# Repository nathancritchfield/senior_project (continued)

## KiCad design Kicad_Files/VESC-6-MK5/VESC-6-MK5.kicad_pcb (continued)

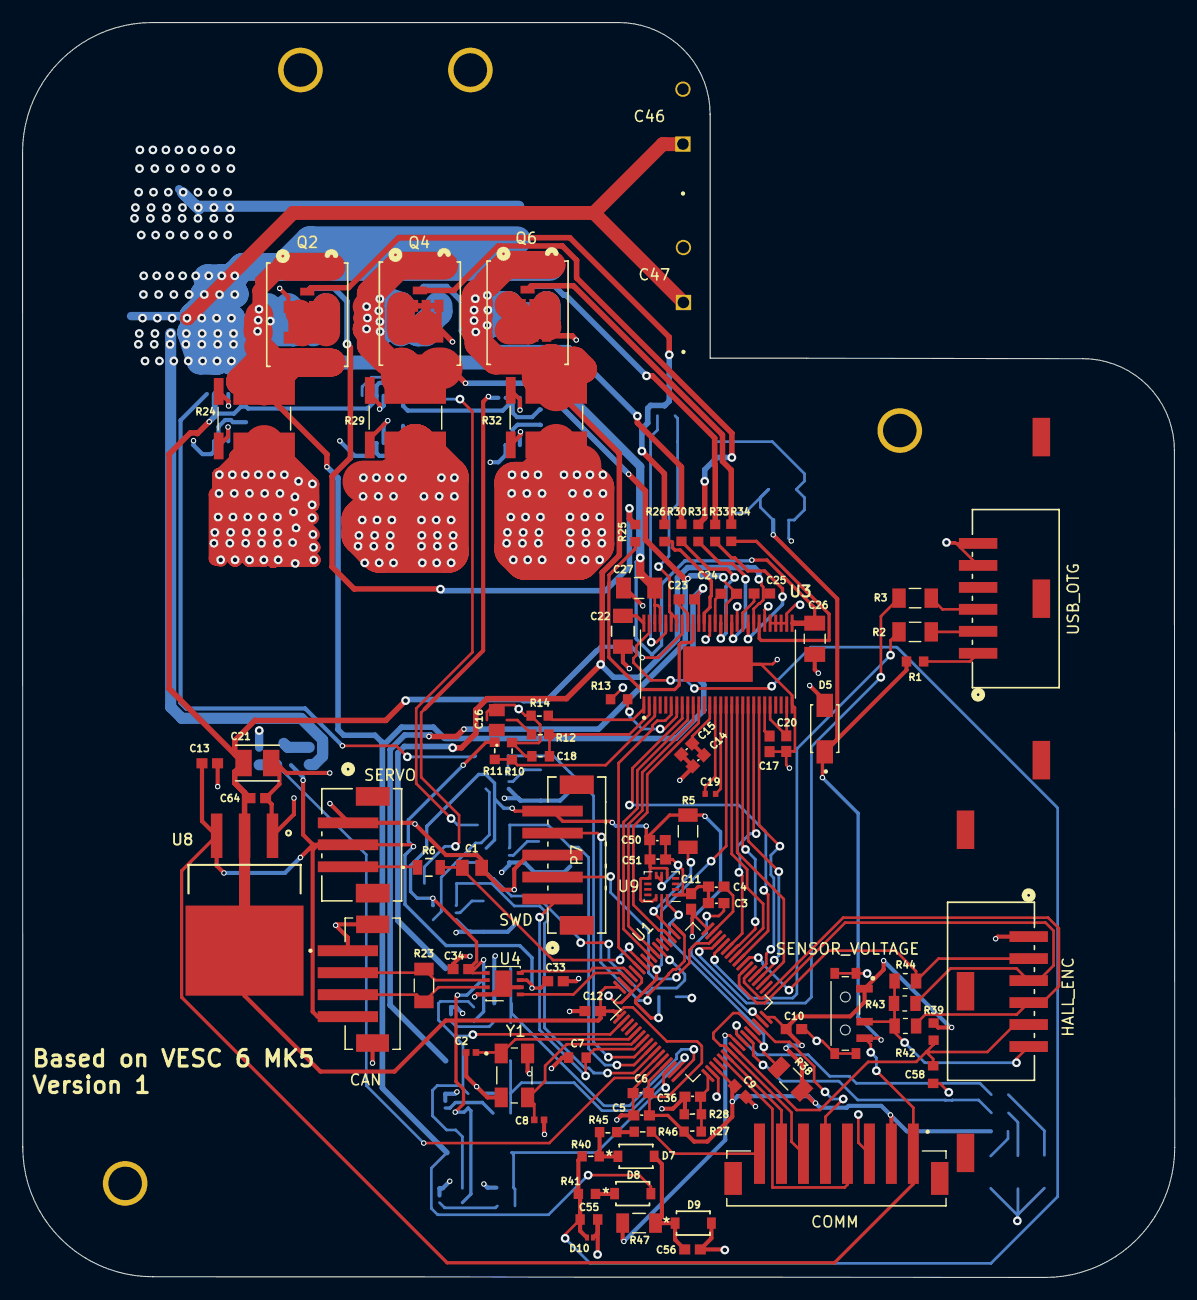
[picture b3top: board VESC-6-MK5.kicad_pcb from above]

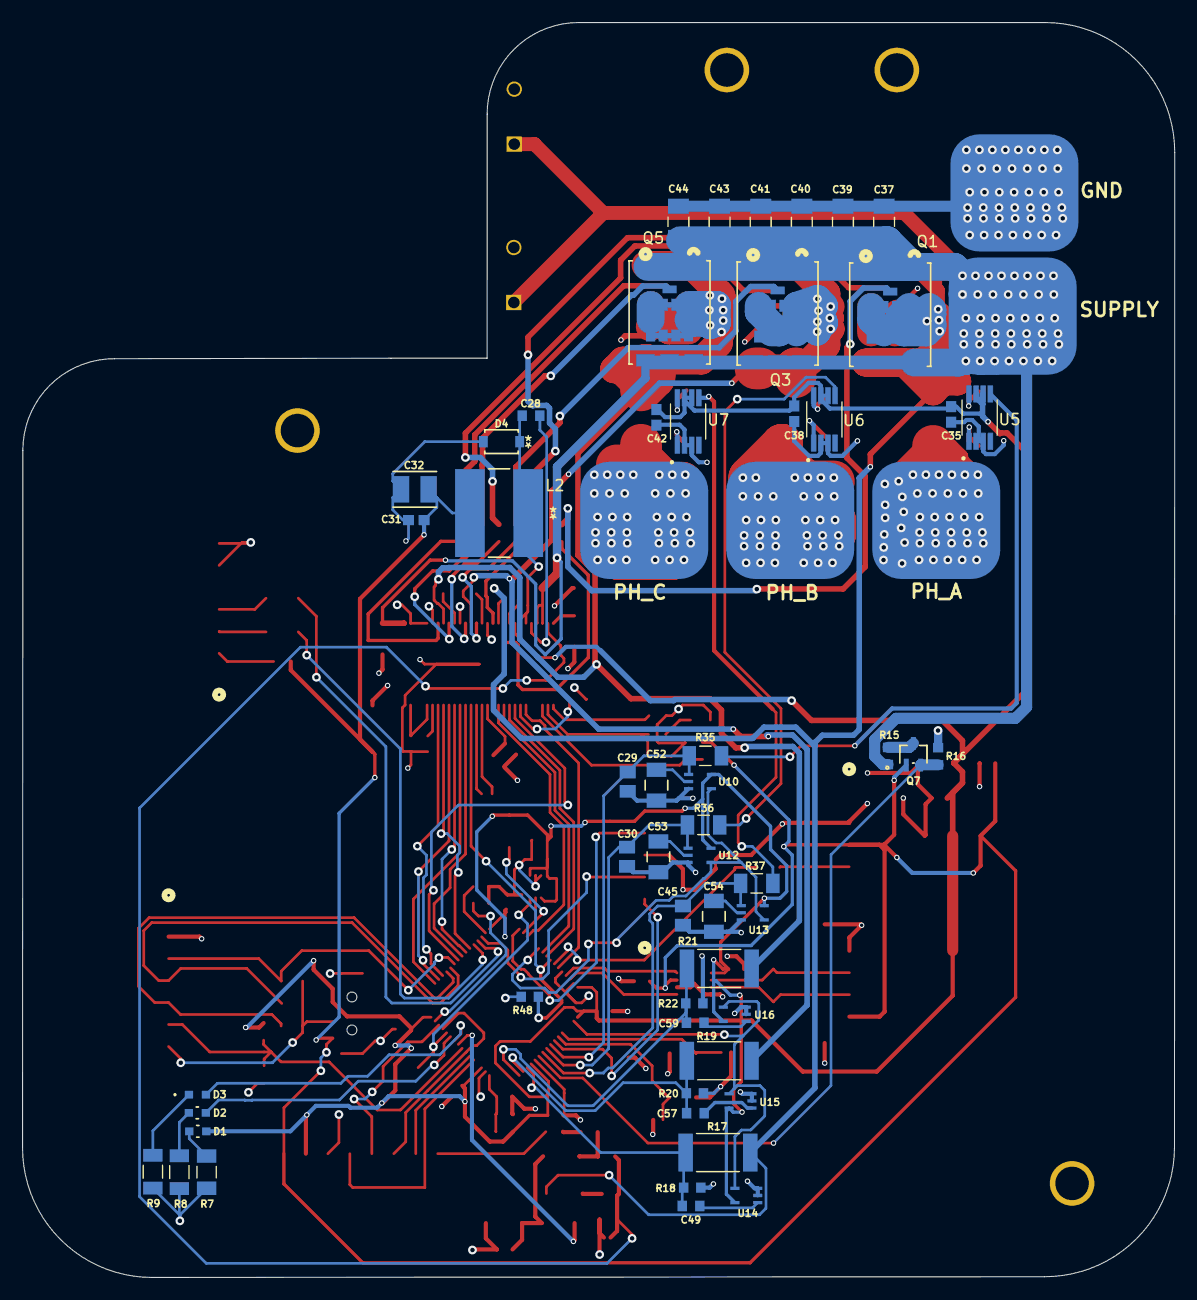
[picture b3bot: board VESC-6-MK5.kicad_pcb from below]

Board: 4 copper layers, 104.8 x 114.2 mm, 150 parts (59 on the bottom side), 117 nets.

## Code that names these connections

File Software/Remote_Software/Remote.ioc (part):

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Mcu.Name=STM32G030F6Px
Mcu.Package=TSSOP20
Mcu.UserName=STM32G030F6Px
PA0.GPIOParameters=GPIO_Speed
PA0.GPIO_Speed=GPIO_SPEED_FREQ_HIGH
PA0.Mode=Simplex_Bidirectional_Master
PA0.Signal=SPI2_SCK
PA1.GPIOParameters=GPIO_Label
PA1.GPIO_Label=Analog_In
PA1.Mode=IN1
PA1.Signal=ADC1_IN1
PA11\ [PA9].GPIOParameters=GPIO_Label
PA11\ [PA9].GPIO_Label=NRF_CE
PA11\ [PA9].Signal=GPIO_Output
PA12\ [PA10].GPIOParameters=GPIO_Label
PA12\ [PA10].GPIO_Label=Button_In
PA12\ [PA10].Signal=GPIO_Input
PA13.Mode=Serial_Wire
PA13.Signal=SYS_SWDIO
PA14-BOOT0.Mode=Serial_Wire
PA14-BOOT0.Signal=SYS_SWCLK
PA14-BOOT0__PA15.StandardMode=true
PA2.Mode=Full_Duplex_Master
PA2.Signal=SPI1_MOSI
PA3.GPIOParameters=GPIO_Label
PA3.GPIO_Label=RST
PA3.Signal=GPIO_Output
PA4.GPIOParameters=GPIO_Speed
PA4.GPIO_Speed=GPIO_SPEED_FREQ_HIGH
PA4.Mode=Simplex_Bidirectional_Master
PA4.Signal=SPI2_MOSI
PA5.Mode=Full_Duplex_Master
PA5.Signal=SPI1_SCK
PA6.Mode=Full_Duplex_Master
PA6.Signal=SPI1_MISO
PA7.GPIOParameters=GPIO_Label
PA7.GPIO_Label=LED
PA7.Signal=GPIO_Output
PB0.GPIOParameters=GPIO_Label
PB0.GPIO_Label=SPI1_CSN
PB0.Signal=GPIO_Output
PB0__PB1__PB2__PA8.StandardMode=true
PB3__PB4__PB5__PB6.StandardMode=true
PB6.Mode=Half_duplex(single_wire_mode)
PB6.Signal=USART1_TX
PB7__PB8.StandardMode=true
PB8.GPIOParameters=GPIO_Label
PB8.GPIO_Label=BL
PB8.Signal=S_TIM16_CH1
PB9.GPIOParameters=GPIO_Label
PB9.GPIO_Label=CS
PB9.Signal=GPIO_Output
PC14-OSC32_IN\ (PC14)__PB9.StandardMode=true
PC15-OSC32_OUT\ (PC15).GPIOParameters=GPIO_Label
PC15-OSC32_OUT\ (PC15).GPIO_Label=DC
PC15-OSC32_OUT\ (PC15).Signal=GPIO_Output
RCC.HSE_VALUE=8000000
RCC.SYSCLKFreq_VALUE=16000000
board=custom

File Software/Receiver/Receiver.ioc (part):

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Mcu.Name=STM32G031F(4-6-8)Px
Mcu.Package=TSSOP20
Mcu.UserName=STM32G031F8Px
PA0.GPIOParameters=GPIO_Label
PA0.GPIO_Label=GEN_OUT
PA0.Signal=GPIO_Output
PA1.Mode=Full_Duplex_Master
PA1.Signal=SPI1_SCK
PA11\ [PA9].GPIOParameters=GPIO_Speed,GPIO_Pu
PA11\ [PA9].GPIO_Pu=GPIO_PULLUP
PA11\ [PA9].GPIO_Speed=GPIO_SPEED_FREQ_VERY_HIGH
PA11\ [PA9].Mode=I2C
PA11\ [PA9].Signal=I2C2_SCL
PA12\ [PA10].GPIOParameters=GPIO_Speed,GPIO_Pu
PA12\ [PA10].GPIO_Pu=GPIO_PULLUP
PA12\ [PA10].GPIO_Speed=GPIO_SPEED_FREQ_VERY_HIGH
PA12\ [PA10].Mode=I2C
PA12\ [PA10].Signal=I2C2_SDA
PA13.Mode=Serial_Wire
PA13.Signal=SYS_SWDIO
PA14-BOOT0.Mode=Serial_Wire
PA14-BOOT0.Signal=SYS_SWCLK
PA14-BOOT0__PA15.StandardMode=true
PA2.Mode=Full_Duplex_Master
PA2.Signal=SPI1_MOSI
PA3.GPIOParameters=GPIO_Label
PA3.GPIO_Label=NRF_CE
PA3.Signal=GPIO_Output
PA4.GPIOParameters=GPIO_Label
PA4.GPIO_Label=SPI1_CSN
PA4.Signal=GPIO_Output
PA5.GPIOParameters=GPIO_Label
PA5.GPIO_Label=SPI1_IRQ
PA5.Signal=GPIO_Input
PA6.Mode=Full_Duplex_Master
PA6.Signal=SPI1_MISO
PA7.GPIOParameters=GPIO_Label
PA7.GPIO_Label=STATUS_LED
PA7.Signal=GPIO_Output
PA8.GPIOParameters=GPIO_Label
PA8.GPIO_Label=PWM_OUT
PA8.Signal=S_TIM1_CH1
PB0__PB1__PB2__PA8.StandardMode=true
PB3__PB4__PB5__PB6.StandardMode=true
PB6.Mode=Asynchronous
PB6.Signal=USART1_TX
PB7.Mode=Asynchronous
PB7.Signal=USART1_RX
PB7__PB8.StandardMode=true
PB9.GPIOParameters=GPIO_Label
PB9.GPIO_Label=WP
PB9.Signal=GPIO_Output
PC14-OSC32_IN\ (PC14)__PB9.StandardMode=true
PC15-OSC32_OUT\ (PC15).GPIOParameters=GPIO_Label
PC15-OSC32_OUT\ (PC15).GPIO_Label=SK6812_OUT
PC15-OSC32_OUT\ (PC15).Signal=GPIO_Output
RCC.HSE_VALUE=8000000
RCC.SYSCLKFreq_VALUE=16000000
board=custom

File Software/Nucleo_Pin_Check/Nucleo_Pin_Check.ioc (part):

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Mcu.Name=STM32L476R(C-E-G)Tx
Mcu.Package=LQFP64
Mcu.UserName=STM32L476RGTx
PA13\ (JTMS-SWDIO).GPIOParameters=GPIO_Label
PA13\ (JTMS-SWDIO).GPIO_Label=TMS
PA13\ (JTMS-SWDIO).Mode=Serial_Wire
PA13\ (JTMS-SWDIO).Signal=SYS_JTMS-SWDIO
PA14\ (JTCK-SWCLK).GPIOParameters=GPIO_Label
PA14\ (JTCK-SWCLK).GPIO_Label=TCK
PA14\ (JTCK-SWCLK).Mode=Serial_Wire
PA14\ (JTCK-SWCLK).Signal=SYS_JTCK-SWCLK
PA2.GPIOParameters=GPIO_Speed,GPIO_PuPd,GPIO_Label,GPIO_Mode
PA2.GPIO_Label=USART_TX
PA2.GPIO_Mode=GPIO_MODE_AF_PP
PA2.GPIO_PuPd=GPIO_NOPULL
PA2.GPIO_Speed=GPIO_SPEED_FREQ_VERY_HIGH
PA2.Mode=Asynchronous
PA2.Signal=USART2_TX
PA3.GPIOParameters=GPIO_Speed,GPIO_PuPd,GPIO_Label,GPIO_Mode
PA3.GPIO_Label=USART_RX
PA3.GPIO_Mode=GPIO_MODE_AF_PP
PA3.GPIO_PuPd=GPIO_NOPULL
PA3.GPIO_Speed=GPIO_SPEED_FREQ_VERY_HIGH
PA3.Mode=Asynchronous
PA3.Signal=USART2_RX
PA5.GPIOParameters=GPIO_Speed,GPIO_PuPd,GPIO_Label,GPIO_ModeDefaultOutputPP
PA5.GPIO_Label=LD2 [green Led]
PA5.GPIO_ModeDefaultOutputPP=GPIO_MODE_OUTPUT_PP
PA5.GPIO_PuPd=GPIO_NOPULL
PA5.GPIO_Speed=GPIO_SPEED_FREQ_LOW
PA5.Signal=GPIO_Output
PB3\ (JTDO-TRACESWO).GPIOParameters=GPIO_Label
PB3\ (JTDO-TRACESWO).GPIO_Label=SWO
PB3\ (JTDO-TRACESWO).Signal=SYS_JTDO-SWO
PC13.GPIOParameters=GPIO_PuPd,GPIO_Label,GPIO_ModeDefaultEXTI
PC13.GPIO_Label=B1 [Blue PushButton]
PC13.GPIO_ModeDefaultEXTI=GPIO_MODE_IT_FALLING
PC13.GPIO_PuPd=GPIO_NOPULL
PC13.Signal=GPXTI13
PC14-OSC32_IN\ (PC14).Mode=LSE-External-Oscillator
PC14-OSC32_IN\ (PC14).Signal=RCC_OSC32_IN
PC15-OSC32_OUT\ (PC15).Mode=LSE-External-Oscillator
PC15-OSC32_OUT\ (PC15).Signal=RCC_OSC32_OUT
PC4.Mode=Asynchronous
PC4.Signal=USART3_TX
PC5.Mode=Asynchronous
PC5.Signal=USART3_RX
PH0-OSC_IN\ (PH0).Signal=RCC_OSC_IN
PH1-OSC_OUT\ (PH1).Signal=RCC_OSC_OUT
RCC.HSE_VALUE=8000000
RCC.SYSCLKFreq_VALUE=80000000
RCC.SYSCLKSource=RCC_SYSCLKSOURCE_PLLCLK
board=NUCLEO-L476RG
boardIOC=true

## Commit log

2023-12-06 Designed PCB hardware
2023-12-07 Switched stunt resistors location
2023-12-07 Moved current sense amplifiers next to the shunt resistors
2023-12-10 Added mounting hardware
2024-01-13 Remote schematic added
2024-01-13 Added footprints
2024-01-15 Finished with remote V1 PCB
2024-02-08 Working sample of the display
2024-02-08 Receiver first commit
2024-02-08 Library's initialization Clear() and SetWindows() functions are working
2024-02-08 GUI_Paint.h functions appear to be functioning
2024-02-08 Added basic demo that counts the number of button presses
2024-02-15 Finished Receiver V1
2024-02-16 Reorganized files
2024-02-17 Raised clock speed and fiexed ADC bug
2024-03-11 Added part of the NRF library. Not yet tested
2024-03-13 Made background white
2024-03-13 Fixing branch
2024-03-20 Put the new MCU on the remote and got the NRF chip working
2024-03-23 Added template for communicating with VESC in Receiver main.c
2024-03-24 Added and tested VESCReceiveMessage and VESCSendMEssage functions
2024-03-24 Added missing folders
2024-04-08 Minimal functionality @ 10 amp maximum current
2024-04-30 Working with screen
